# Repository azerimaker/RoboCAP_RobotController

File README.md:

# RoboCAP Robot Controller
ATmega328 based Robot Remote Controller and Receiver Circuit. [Read more.](http://makerspace-az.org/az/elektronika/robocap-v-1-0-robot-controller/)

<div align="center">
<br /> This work is licensed under a <a rel="license" href="http://creativecommons.org/licenses/by-sa/4.0/">Creative Commons Attribution-ShareAlike 4.0 International License</a>.

</div>

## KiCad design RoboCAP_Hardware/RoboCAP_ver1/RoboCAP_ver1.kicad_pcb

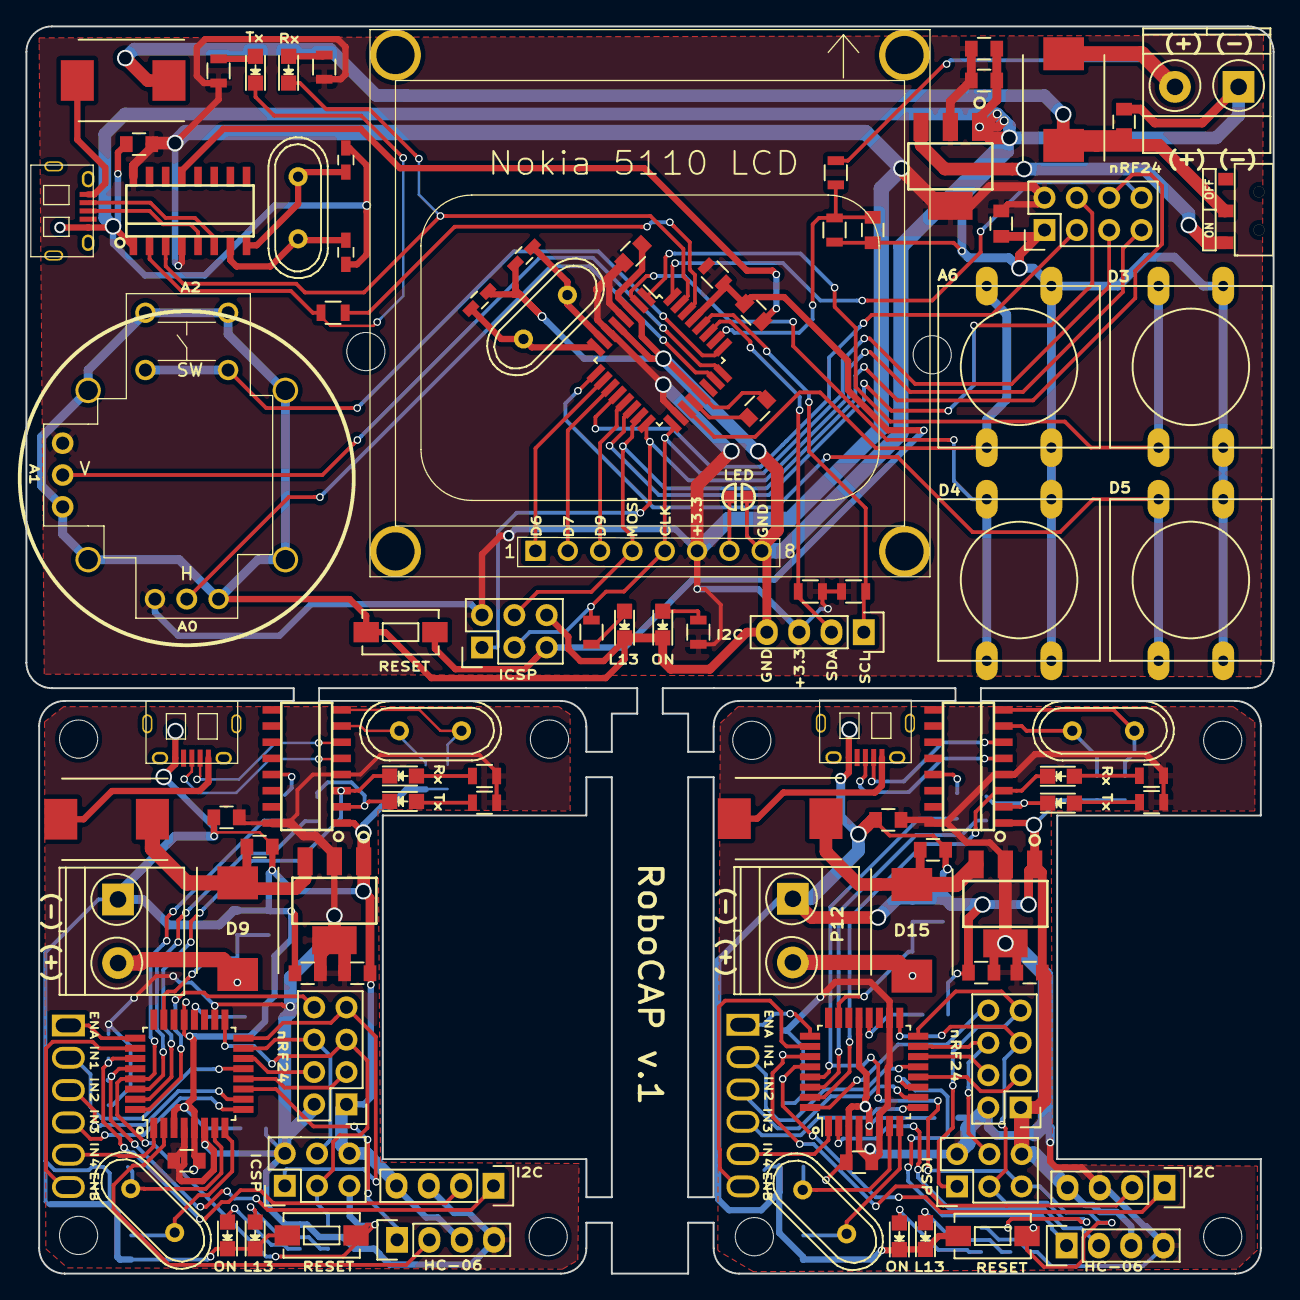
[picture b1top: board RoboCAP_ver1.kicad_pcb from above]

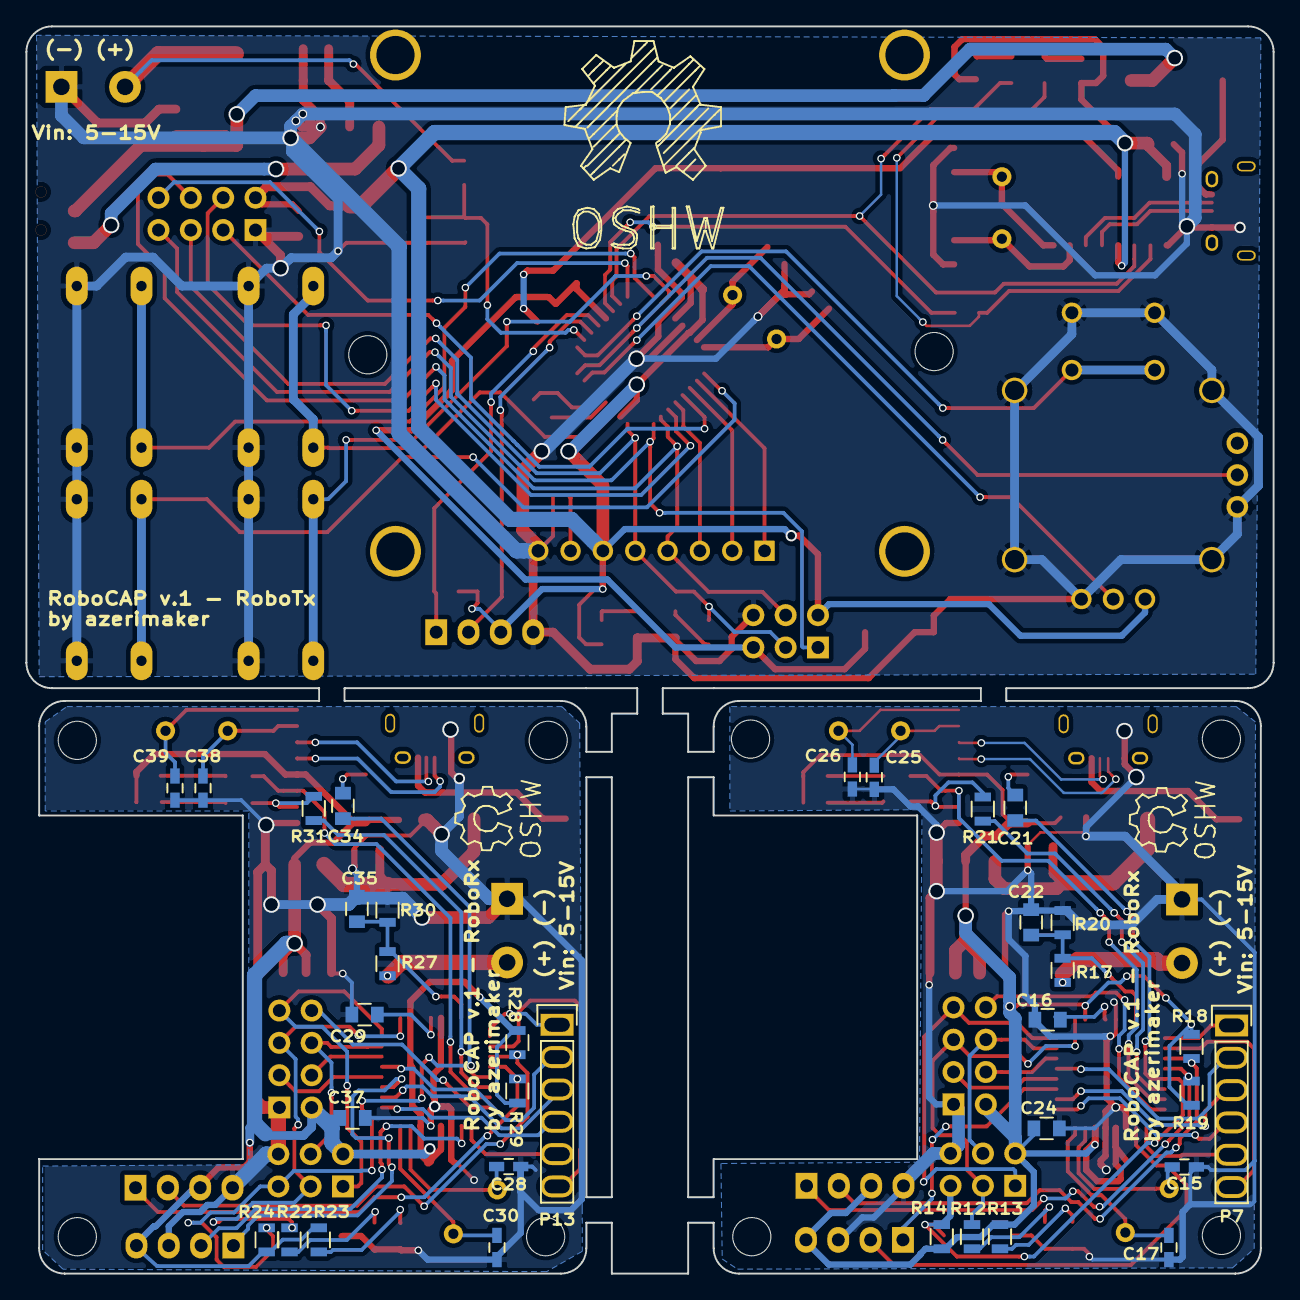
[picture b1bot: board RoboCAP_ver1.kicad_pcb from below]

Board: 2 copper layers, 98.0 x 98.0 mm, 132 parts (34 on the bottom side), 110 nets.

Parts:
C1, C2, C6, C8, C9, C10, C14, C16, C18, C21, C22, C23, C27, C29, C31, C34, C35, C36: 100nF; C_0805
C3, C13, C19, C24, C32, C37: 10uF; C_0805
C4, C20, C33: 10uF, 35V; C_0805
C5, C7, C11, C12, C15, C17, C25, C26, C28, C30, C38, C39: 22pF; C_0603_HandSoldering
D1, D2, D8, D9, D14, D15: MBR0520; DO-214AB
D3, D10, D16: ON_LED; LED_0805
D4, D7, D13: LED; LED_0805
D5, D11, D17: RX_LED; LED_0805
D6, D12, D18: TX_LED; LED_0805
IC1, IC2, IC3: ATMEGA328P-AU; TQFP-32_7x7mm_Pitch0.8mm
P1, P6, P12: Vin 5-15V; TerminalBlock_Pheonix_MKDS1.5-2pol
P2, P9, P16: I2C_CONN; Pin_Header_Straight_1x04
P3, P8, P15: nRF24L01_CONN; Pin_Header_Straight_2x04
P4: Joystick
P5, P11, P17: ICSP_CONN; Pin_Header_Straight_2x03
P7, P13: L298N_CONN; Pin_Header_Straight_1x06
P10, P14: HC-06_CONN; Pin_Header_Straight_1x04
R1, R2, R4, R5, R6, R12, R13, R15, R16, R21, R22, R23, R25, R26, R31: 1K; R_0805
R3, R8, R9, R14, R18, R19, R24, R28, R29: 10K; R_0805
R7, R17, R27: 100K; R_0805
R10: 33K; R_0805
R11: 0R; SOLDER-JUMPER_1-WAY
R20, R30: 22K; R_0805
SW1: Switch_SPDT; AYZ0102AGRLC
SW2, SW7, SW8: RESET; SW_SPST_EVQPE1
SW3: SW_UP; SW_PUSH-12mm
SW4: SW_LEFT; SW_PUSH-12mm
SW5: SW_RIGHT; SW_PUSH-12mm
SW6: SW_DOWN; SW_PUSH-12mm
U1, U5, U8: AMS1117-33; SOT223
U2, U6, U9: CH340G; SOIC16
U3, U7, U10: MICRO-B_USB; Micro_USB_TH
U4: Nokia 5110 LCD; Nokia_5110_LCD
Y1, Y3, Y5: 8MHz_HC49; Crystal_HC49-U_Vertical
Y2, Y4, Y6: 12MHz_HC49; Crystal_HC49-U_Vertical

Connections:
+3V3: C1.1, C2.1, C3.1, C9.1, C13.1, C14.1, C18.1, C19.1, C23.1, C24.1, C27.1, C31.1, C32.1, C36.1, C37.1, IC1.4, IC1.6, IC1.18, IC2.4, IC2.6, IC2.18, IC3.4, IC3.6, IC3.18, P2.3, P3.2, P4.1, P4.4, P5.2, P8.2, P9.3, P10.4, P11.2, P14.4, P15.2, P16.3, P17.2, R1.2, R3.2, R4.2, R5.2, R8.2, R9.2, R13.2, R14.2, R15.2, R16.2, R18.2, R19.2, R23.2, R24.2, R25.2, R26.2, R28.2, R29.2, U1.2, U1.4, U2.4, U2.16, U4.6, U5.2, U5.4, U6.4, U6.16, U8.2, U8.4, U9.4, U9.16
+5V: D1.2, D8.2, D14.2, U3.1, U7.1, U10.1
+BATT: D2.2, D9.2, D15.2, P1.2, P6.2, P12.2, R7.2, R17.2, R27.2
/RoboCAP_Rx1/A0: C22.2, IC2.23, R17.1, R20.2
/RoboCAP_Rx1/A2: IC2.25, P7.1
/RoboCAP_Rx1/A3: IC2.26, P7.6
/RoboCAP_Rx1/A4: IC2.27, P9.2, R18.1
/RoboCAP_Rx1/A5: IC2.28, P9.1, R19.1
/RoboCAP_Rx1/AREF: C16.1, IC2.20
/RoboCAP_Rx1/D0/RX: IC2.30, R21.1
/RoboCAP_Rx1/D1/TX: D11.1, IC2.31, U6.3
/RoboCAP_Rx1/D2: IC2.32, P8.8
/RoboCAP_Rx1/D3: IC2.1, P7.5
/RoboCAP_Rx1/D4: IC2.2, P10.2
/RoboCAP_Rx1/D5: IC2.9, P7.4
/RoboCAP_Rx1/D6: IC2.10, P7.3
/RoboCAP_Rx1/D7: IC2.11, P10.1
/RoboCAP_Rx1/D8: IC2.12, P8.3
/RoboCAP_Rx1/D9: IC2.13, P7.2
/RoboCAP_Rx1/D10: IC2.14, P8.4
/RoboCAP_Rx1/D11/MOSI: IC2.15, P8.6, P11.4
/RoboCAP_Rx1/D12/MISO: IC2.16, P8.7, P11.1
/RoboCAP_Rx1/D13/SCK: IC2.17, P8.5, P11.3, R12.2
/RoboCAP_Rx1/DTR: C21.1, U6.13
/RoboCAP_Rx1/RESET: C21.2, IC2.29, P11.5, R14.1, SW7.1
/RoboCAP_Rx1/TX: D12.1, R21.2, U6.2
/RoboCAP_Rx2/A0: C35.2, IC3.23, R27.1, R30.2
/RoboCAP_Rx2/A2: IC3.25, P13.1
/RoboCAP_Rx2/A3: IC3.26, P13.6
/RoboCAP_Rx2/A4: IC3.27, P16.2, R28.1
/RoboCAP_Rx2/A5: IC3.28, P16.1, R29.1
/RoboCAP_Rx2/AREF: C29.1, IC3.20
/RoboCAP_Rx2/D0/RX: IC3.30, R31.1
/RoboCAP_Rx2/D1/TX: D17.1, IC3.31, U9.3
/RoboCAP_Rx2/D2: IC3.32, P15.8
/RoboCAP_Rx2/D3: IC3.1, P13.5
/RoboCAP_Rx2/D4: IC3.2, P14.2
/RoboCAP_Rx2/D5: IC3.9, P13.4
/RoboCAP_Rx2/D6: IC3.10, P13.3
/RoboCAP_Rx2/D7: IC3.11, P14.1
/RoboCAP_Rx2/D8: IC3.12, P15.3
/RoboCAP_Rx2/D9: IC3.13, P13.2
/RoboCAP_Rx2/D10: IC3.14, P15.4
/RoboCAP_Rx2/D11/MOSI: IC3.15, P15.6, P17.4
/RoboCAP_Rx2/D12/MISO: IC3.16, P15.7, P17.1
/RoboCAP_Rx2/D13/SCK: IC3.17, P15.5, P17.3, R22.2
/RoboCAP_Rx2/DTR: C34.1, U9.13
/RoboCAP_Rx2/RESET: C34.2, IC3.29, P17.5, R24.1, SW8.1
/RoboCAP_Rx2/TX: D18.1, R31.2, U9.2
/RoboCAP_Tx/A0: IC1.23, P4.5
/RoboCAP_Tx/A1: IC1.24, P4.2
/RoboCAP_Tx/A2: IC1.25, P4.7, P4.8
/RoboCAP_Tx/A3: C10.1, IC1.26, R7.1, R10.2
/RoboCAP_Tx/A4: IC1.27, P2.2, R8.1
/RoboCAP_Tx/A5: IC1.28, P2.1, R9.1
/RoboCAP_Tx/A6: IC1.19, SW3.1
/RoboCAP_Tx/AREF: C6.1, IC1.20
/RoboCAP_Tx/D0/RX: IC1.30, R6.1
/RoboCAP_Tx/D1/TX: D5.1, IC1.31, U2.3
/RoboCAP_Tx/D2: IC1.32, P3.8
/RoboCAP_Tx/D3: IC1.1, SW5.2
/RoboCAP_Tx/D4: IC1.2, SW4.1
/RoboCAP_Tx/D5: IC1.9, SW6.1
/RoboCAP_Tx/D6: IC1.10, U4.1
/RoboCAP_Tx/D7: IC1.11, U4.2
/RoboCAP_Tx/D8: IC1.12, P3.3
/RoboCAP_Tx/D9: IC1.13, U4.3
/RoboCAP_Tx/D10: IC1.14, P3.4
/RoboCAP_Tx/D11/MOSI: IC1.15, P3.6, P5.4, U4.4
/RoboCAP_Tx/D12/MISO: IC1.16, P3.7, P5.1
/RoboCAP_Tx/D13/SCK: IC1.17, P3.5, P5.3, R2.2, U4.5
/RoboCAP_Tx/DTR: C8.1, U2.13
/RoboCAP_Tx/RESET: C8.2, IC1.29, P5.5, R3.1, SW2.1
/RoboCAP_Tx/TX: D6.1, R6.2, U2.2
GND: C1.2, C2.2, C3.2, C4.2, C5.1, C6.2, C7.1, C9.2, C10.2, C11.2, C12.2, C13.2, C14.2, C15.1, C16.2, C17.1, C18.2, C19.2, C20.2, C22.1, C23.2, C24.2, C25.2, C26.2, C27.2, C28.1, C29.2, C30.1, C31.2, C32.2, C33.2, C35.1, C36.2, C37.2, C38.2, C39.2, D3.1, D4.1, D7.1, D10.1, D13.1, D16.1, IC1.3, IC1.5, IC1.21, IC2.3, IC2.5, IC2.21, IC3.3, IC3.5, IC3.21, P1.1, P2.4, P3.1, P4.3, P4.6, P4.9, P4.10, P4.11, P4.12, P4.13, P4.14, P5.6, P6.1, P8.1, P9.4, P10.3, P11.6, P12.1, P14.3, P15.1, P16.4, P17.6, R10.1, R11.2, R20.1, R30.1, SW2.2, SW3.2, SW4.2, SW5.1, SW6.2, SW7.2, SW8.2, U1.1, U2.1, U3.5, U4.8, U5.1, U6.1, U7.5, U8.1, U9.1, U10.5
unnamed: C4.1, D1.1, D2.1, SW1.2
unnamed: C5.2, IC1.7, Y1.1
unnamed: C7.2, IC1.8, Y1.2
unnamed: C11.1, U2.7, Y2.1
unnamed: C12.1, U2.8, Y2.2
unnamed: C15.2, IC2.7, Y3.1
unnamed: C17.2, IC2.8, Y3.2
unnamed: C20.1, D8.1, D9.1, U5.3
unnamed: C25.1, U6.7, Y4.1
unnamed: C26.1, U6.8, Y4.2
unnamed: C28.2, IC3.7, Y5.1
unnamed: C30.2, IC3.8, Y5.2
unnamed: C33.1, D14.1, D15.1, U8.3
unnamed: C38.1, U9.7, Y6.1
unnamed: C39.1, U9.8, Y6.2
unnamed: D3.2, R1.1
unnamed: D4.2, R2.1
unnamed: D5.2, R4.1
unnamed: D6.2, R5.1
unnamed: D7.2, R12.1
unnamed: D10.2, R13.1
unnamed: D11.2, R15.1
unnamed: D12.2, R16.1
unnamed: D13.2, R22.1
unnamed: D16.2, R23.1
unnamed: D17.2, R25.1
unnamed: D18.2, R26.1
unnamed: R11.1, U4.7
unnamed: SW1.1, U1.3
unnamed: U2.5, U3.3
unnamed: U2.6, U3.2
unnamed: U6.5, U7.3
unnamed: U6.6, U7.2
unnamed: U9.6, U10.2
unnamed: U9.5, U10.3

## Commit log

2016-12-01 RoboCAP firmware and board files added
2016-12-01 LCD test added
2016-12-18 edited
2016-12-18 fix Analog read
2017-01-17 improved speed
2017-01-17 design files added
2017-01-17 readme
2017-10-29 Nokia 5110 LCD Screen
    Test code for Nokia 5110 LCD Screen
2018-05-24 added-NokiaLCD
2018-05-24 RoboCap-Driver-improvements
    added failsafe
